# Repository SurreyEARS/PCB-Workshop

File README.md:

# PCB-Workshop
SurreyEARS workshop on designing simple development boards - "gEARS".

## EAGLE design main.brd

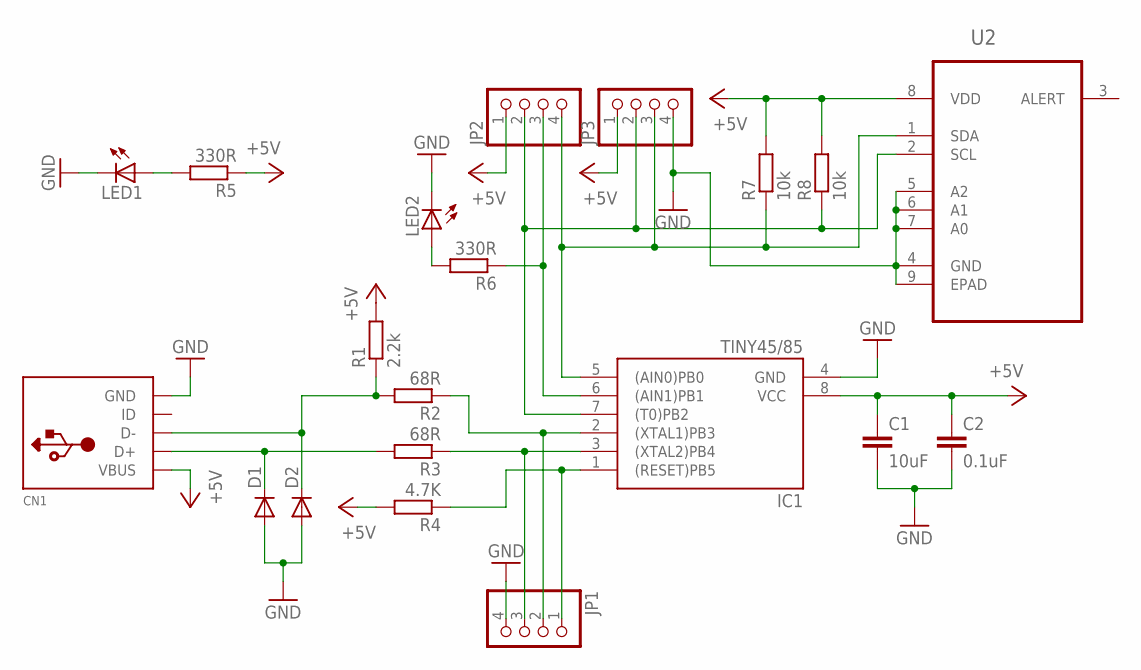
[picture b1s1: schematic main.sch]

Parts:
C1: 10uF; C0805
C2: 0.1uF; C0805
CN1: USBMINIB; USB-MINIB
D1, D2: DIODE-SOD323-W; SOD323-W
IC1: TINY45/85; SOIC8
JP1, JP2, JP3: PINHD-1X4; 1X04
LED1, LED2: LEDCHIPLED_0603; CHIPLED_0603
R1: 2.2k; R0805
R2, R3: 68R; R0805
R4: 4.7K; R0805
R5, R6: 330R; R0805
R7, R8: 10k; R0805
U2: MCP9808T-E/MC; DFN300X200X100-9N

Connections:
+5V: C1.1, C2.1, CN1.VBUS, IC1.8 (VCC), JP2.1, JP3.1, R1.2, R4.2, R5.1, R7.2, R8.2
GND: C1.2, C2.2, CN1.GND, D1.A, D2.A, IC1.4 (GND), JP1.4, JP3.4, LED1.C, LED2.C, U2.4 (GND), U2.5 (A2), U2.6 (A1), U2.7 (A0), U2.9 (EPAD)
unnamed: IC1.2 ((XTAL1)PB3), JP1.2, R2.1
unnamed: LED1.A, R5.2
unnamed: IC1.6 ((AIN1)PB1), JP2.3, R6.1
unnamed: LED2.A, R6.2
unnamed: IC1.7 ((T0)PB2), JP2.2, JP3.2, R8.1, U2.2 (SCL)
unnamed: IC1.1 ((RESET)PB5), JP1.1, R4.1
unnamed: IC1.3 ((XTAL2)PB4), JP1.3, R3.1
unnamed: CN1.D-, D2.C, R1.1, R2.2
unnamed: IC1.5 ((AIN0)PB0), JP2.4, JP3.3, R7.1, U2.1 (SDA)
unnamed: CN1.D+, D1.C, R3.2
VDD: U2.8 (VDD)

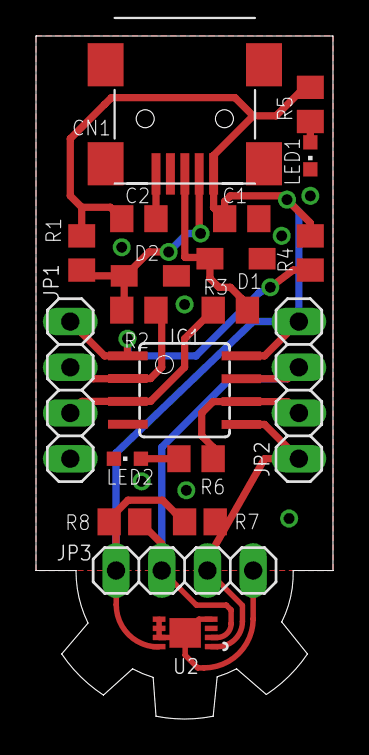
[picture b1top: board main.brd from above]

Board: 2 copper layers, 16.5 x 37.9 mm, 20 parts (0 on the bottom side), 12 nets.

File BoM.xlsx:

| No. Units to be made: | 20 | Total Cost: | 102.26900000000001
 |  |  | Per Unit: | 5.1134500000000003
 | Schematic Reference | Qty/unit | Value or P/N | Package | Price/unit | Minimum QTY | Qty to order | Total | Supplier | Supplier order code
 | R1 | 1 | 2.2K | 0805 | 1.8E-3 | 100 | 100 | 0.18 | Onecall | 2447623
 | R2 R3 | 2 | 68R | 0805 | 8.5000000000000006E-3 | 50 | 50 | 0.42500000000000004 | Onecall | 2138823
 | R4 | 1 | 4.7K | 0805 | 5.5999999999999999E-3 | 50 | 50 | 0.27999999999999997 | Onecall | 9234098
 | R5 R6 | 2 | 330R | 0805 | 1.8E-3 | 100 | 100 | 0.18 | Onecall | 2447638
 | R7 R8 | 2 | 10K | 0805 | 1.8E-3 | 100 | 100 | 0.18 | Onecall | 2447553
 | C1 | 1 | 10uF | 0805 | 0.03 | 100 | 100 | 3 | Onecall | CA06400
 | C2 | 1 | 0.1uF | 0805 | 7.0000000000000001E-3 | 100 | 100 | 0.70000000000000007 | Onecall | CA06475
 | D1 D3 | 2 | 3.6V | SOD323-W | 3.1199999999999999E-2 | 10 | 40 | 1.248 | Onecall | 8735654
 | LED1 | 1 | RED | CHIPLED 0603 | 5.4100000000000002E-2 | 1 | 20 | 1.0820000000000001 | Onecall | 1226372
 | LED2 | 1 | GREEN | CHIPLED 0603 | 5.62E-2 | 1 | 20 | 1.1240000000000001 | Onecall | 2099221
 | IC1 | 1 | ATTINY85-20PU | SOIC-8 | 1.05 | 1 | 20 | 21 | Onecall | 1455164
 | U1 | 1 | MCP9808T-E/MC | DNF | 0.71699999999999997 | 10 | 20 | 14.34 | Onecall | 2080524
 | X1 | 1 | 10033526-N3212MLF | Mini USB | 0.31900000000000001 | 10 | 20 | 6.38 | Onecall | 2112367
 | JP2 JP3 | 2 | 4-pin | 0.1" |  | 100 | 100 | 2.15 | eBay | http://www.ebay.co.uk/itm/10-x-40-Pin-Header-Pins-Strip-PCB-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
 | PCB | 1 |  |  | 2.5 |  | 20 | 50 | Ragworm | http://www.ragworm.eu

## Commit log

2015-03-07 Initial commit
    - Schematic & PCB
    - Modified atmel library adding attiny45/85
    - Sparkfun sensor library
2015-03-07 Added gear cutout and name
2015-03-07 Removed ground plane
    Removed the ground plane from the "gEAR" addon part
2015-03-16 Added EARS Logo
    Added EARS logo to the underside of the PCB. Used a scale factor of
    0.75
2015-04-06 Replaced USB socket
    replace USB socket with the 10033526-N3212MLF as per:
    http://goodfet.sourceforge.net/hardware/facedancer20/
2015-04-06 Added Bill of Materials
    Missing PCB and temperature sensor
2015-04-09 changed sensor. sorted silk.
2015-04-09 Shifted some silk, down the bazaar like. Added via to allow ground plane between I2C lines. Added gerbers.
2015-04-09 Tidy up
    - Removed EAGLE backup files
    - Moved part libraries into folder
    - Added gitignore
2015-04-09 Updated BoM
    Added temperature sensor and PCB
2015-04-10 Fixed text, added pull ups.
2015-04-10 Pulled BoM.xlsx, also changed pull ups to 0805
2015-04-10 Update README.md
    changed image
2015-04-10 Fixed trace
2015-04-16 added eagleup and render
